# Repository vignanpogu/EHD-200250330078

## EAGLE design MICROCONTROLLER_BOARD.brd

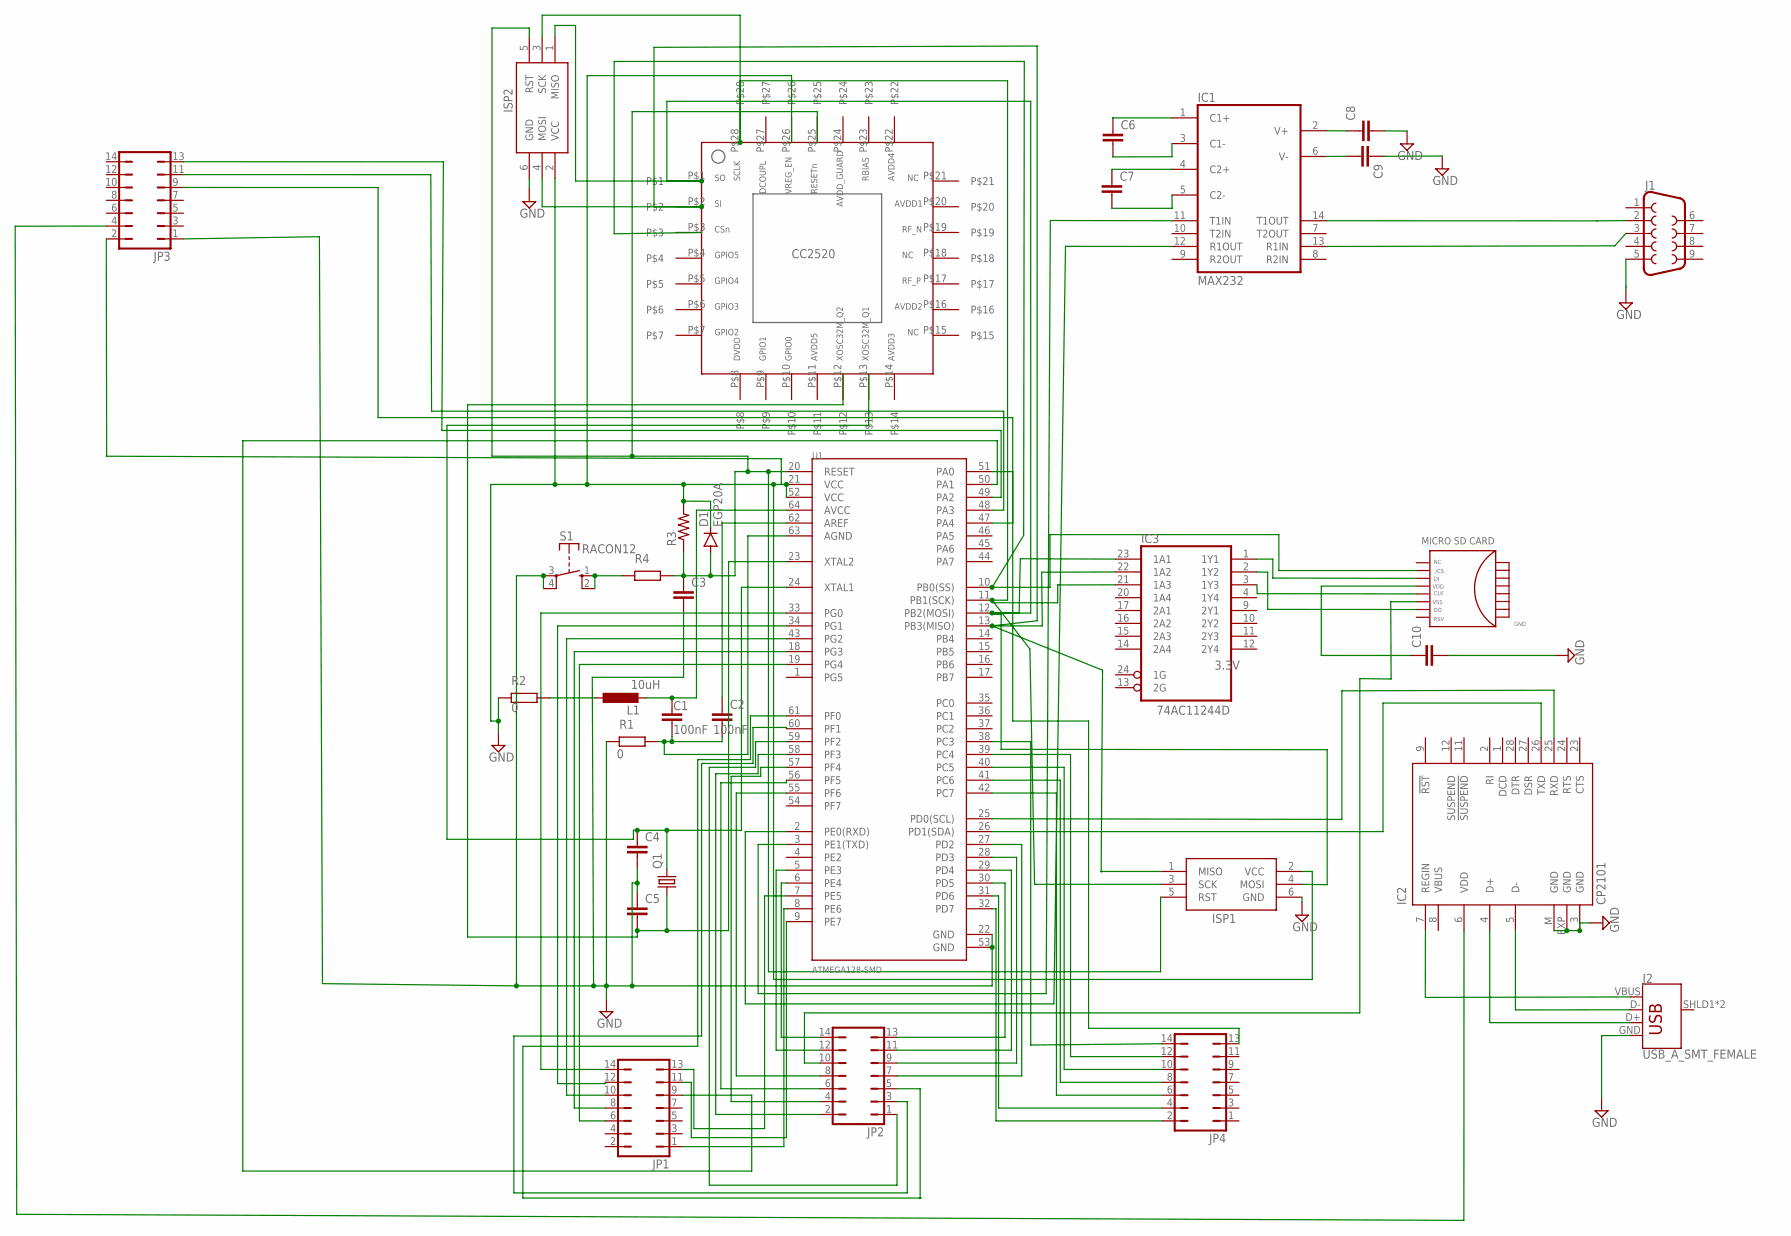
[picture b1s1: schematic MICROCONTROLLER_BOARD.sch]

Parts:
C1, C2, C4, C5: C2,5-3; C2.5-3
C3, C6, C7, C8, C9, C10: C7.5/3; C7.5B3
D1: EGP20A; DO15-12
IC1: MAX232; DIL16
IC2: CP2101; MLP28
IC3: 74AC11244D; SO24W
ISP1, ISP2: AVRISP-6; AVRISP
J1: DB9FEMALE; DB9
J2: USB_A_SMT_FEMALE; USB-A-S-SILK-FEMALE
JP1, JP2, JP3, JP4: JP7Q
L1: L-EU0204/5; 0204/5
Q1: CRYSTALHC49U-V; HC49U-V
R3: R-US_VTA55; VTA55
S1: RACON12
U1: ATMEGA128-SMD; TQFP64_14X14MM
U$1: SD-CARD
U$2: CC2520

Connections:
3.3V: C10.1, U$1.P$4
5V: C3.2, C4.2, C5.1, D1.C, IC1.15 (GND), IC3.5 (GND), IC3.6 (GND), IC3.7 (GND), IC3.8 (GND), ISP1.2 (VCC), ISP2.2 (VCC), JP3.1, JP3.2, R3.2, S1.3, S1.4, U1.21 (VCC), U1.22 (GND), U1.52 (VCC), U1.53 (GND), U$2.P$26
GND: C8.2, C9.1, C10.2, IC2.3 (GND), IC2.EXP (GND), IC2.M (GND), ISP1.6 (GND), ISP2.6 (GND), J1.5, J2.GND
unnamed: C2.1, U1.62 (AREF)
unnamed: C1.2, C2.2, U1.63 (AGND)
unnamed: C1.1, L1.2, U1.64 (AVCC)
unnamed: S1.1 (S), S1.2 (S)
unnamed: C6.1, IC1.1 (C1+)
unnamed: U1.10 (PB0(SS)), U$1.P$2, U$2.P$3
unnamed: C4.1, Q1.2, U1.24 (XTAL1), U$2.P$13
unnamed: C5.2, Q1.1, U1.23 (XTAL2), U$2.P$12
unnamed: IC3.22 (1A2), ISP1.1 (MISO), ISP2.4 (MOSI), U1.13 (PB3(MISO)), U$2.P$2
unnamed: IC3.23 (1A1), ISP1.4 (MOSI), ISP2.1 (MISO), U1.12 (PB2(MOSI)), U$2.P$1
unnamed: IC3.21 (1A3), ISP1.3 (SCK), ISP2.3 (SCK), U1.11 (PB1(SCK)), U$2.P$28
unnamed: C9.2, IC1.6 (V-)
unnamed: C8.1, IC1.2 (V+)
unnamed: C7.1, IC1.4 (C2+)
unnamed: C6.2, IC1.3 (C1-)
unnamed: C7.2, IC1.5 (C2-)
unnamed: IC2.25 (RXD), U1.25 (PD0(SCL))
unnamed: IC1.11 (T1IN), U1.3 (PE1(TXD))
unnamed: IC1.12 (R1OUT), U1.2 (PE0(RXD))
unnamed: IC3.3 (1Y3), U$1.P$5
unnamed: JP2.5, U1.61 (PF0)
unnamed: IC2.5 (D-), J2.D-
unnamed: JP2.3, U1.60 (PF1)
unnamed: IC2.4 (D+), J2.D+
unnamed: IC2.7 (REGIN), J2.VBUS
unnamed: IC1.14 (T1OUT), J1.2
unnamed: IC1.13 (R1IN), J1.3
unnamed: C3.1, D1.A, ISP1.5 (RST), ISP2.5 (RST), R3.1, U1.20 (RESET), U$2.P$25
unnamed: IC2.26 (TXD), U1.26 (PD1(SDA))
unnamed: IC3.1 (1Y1), U$1.P$3
unnamed: IC3.2 (1Y2), U$1.P$7
unnamed: JP2.12, U1.5 (PE3)
unnamed: JP2.14, U1.6 (PE4)
unnamed: JP4.2, U1.32 (PD7)
unnamed: JP4.4, U1.31 (PD6)
unnamed: JP4.12, U1.39 (PC4)
unnamed: JP4.10, U1.40 (PC5)
unnamed: JP4.8, U1.41 (PC6)
unnamed: JP4.6, U1.42 (PC7)
unnamed: JP4.13, U1.51 (PA0)
unnamed: JP1.11, U1.9 (PE7)
unnamed: JP1.1, U1.8 (PE6)
unnamed: JP1.13, U1.7 (PE5)
unnamed: JP1.9, U1.50 (PA1)
unnamed: JP4.14, U1.38 (PC3)
unnamed: JP1.14, U1.33 (PG0)
unnamed: JP1.12, U1.34 (PG1)
unnamed: JP1.10, U1.43 (PG2)
unnamed: JP1.8, U1.18 (PG3)
unnamed: JP1.6, U1.19 (PG4)
unnamed: JP2.13, U1.30 (PD5)
unnamed: JP2.11, U1.29 (PD4)
unnamed: JP2.9, U1.28 (PD3)
unnamed: JP2.7, U1.27 (PD2)
unnamed: JP2.1, U1.59 (PF2)
unnamed: JP2.2, U1.58 (PF3)
unnamed: JP2.4, U1.57 (PF4)
unnamed: JP2.6, U1.56 (PF5)
unnamed: JP2.8, U1.55 (PF6)
unnamed: JP2.10, U$1.P$6
unnamed: JP3.13, U1.49 (PA2)
unnamed: JP3.11, U1.48 (PA3)
unnamed: JP3.9, U1.47 (PA4)
unnamed: IC2.6 (VDD), JP3.4
VCC: IC1.16 (VCC), IC3.18 (VCC), IC3.19 (VCC)

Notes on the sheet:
100nF
10uH

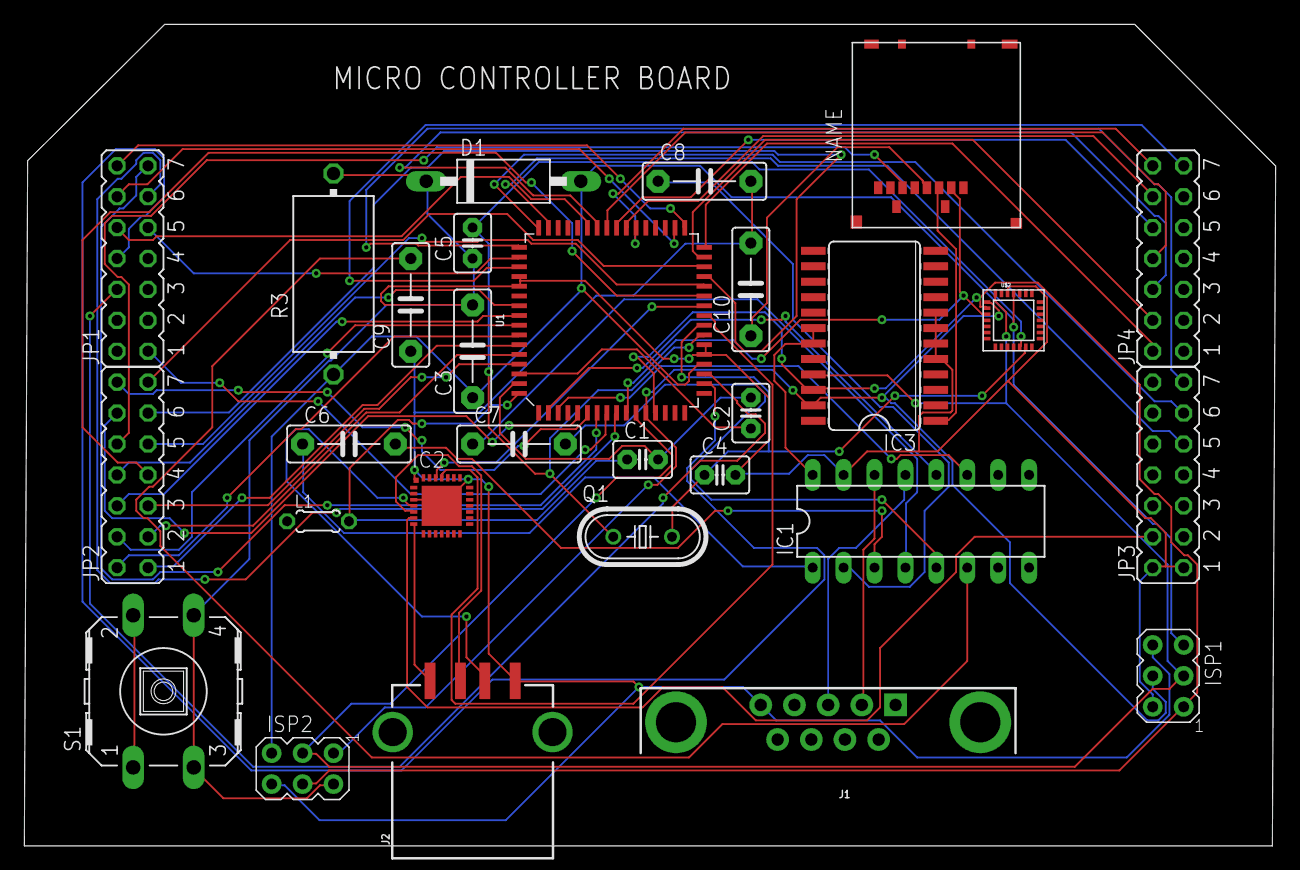
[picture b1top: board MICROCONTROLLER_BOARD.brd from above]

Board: 2 copper layers, 102.8 x 67.5 mm, 29 parts (0 on the bottom side), 68 nets.

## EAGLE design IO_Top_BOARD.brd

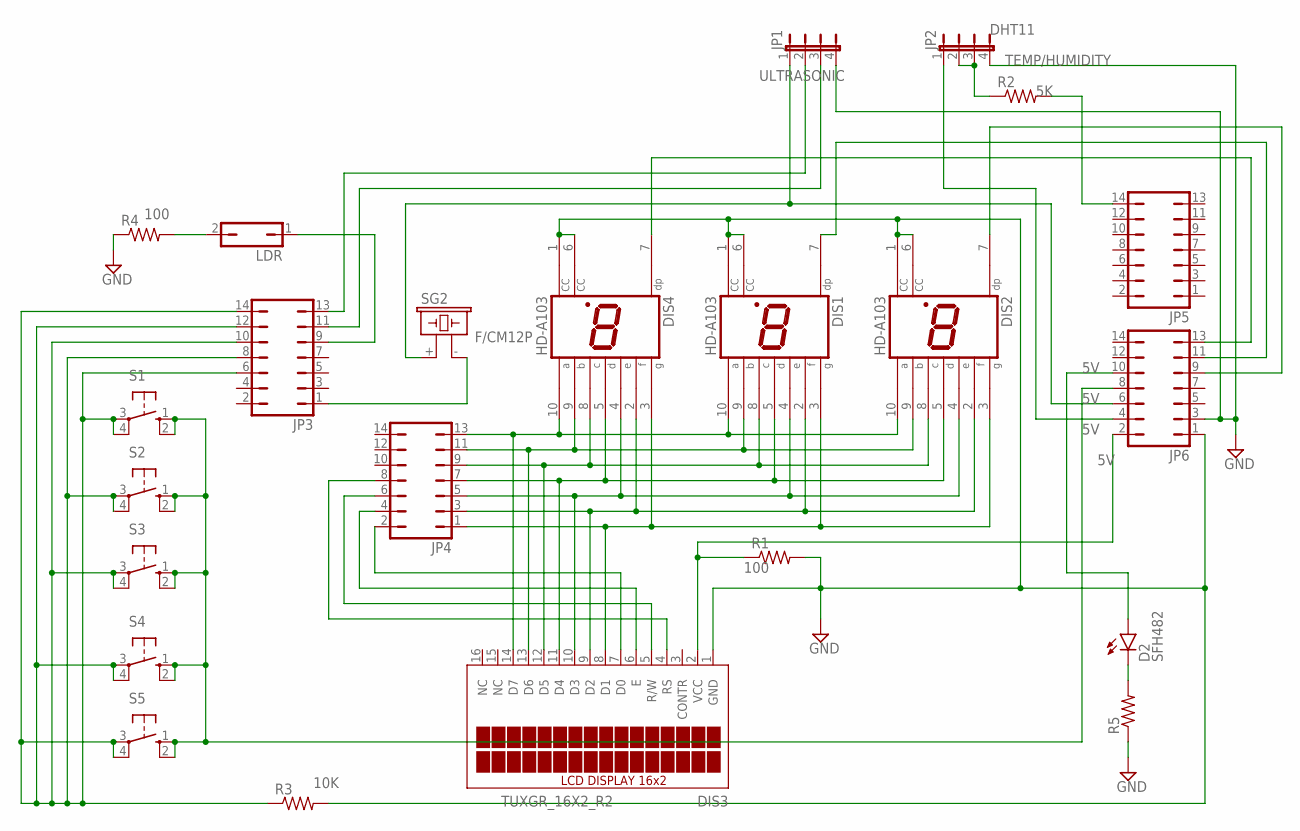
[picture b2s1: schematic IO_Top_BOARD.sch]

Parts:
D2: SFH482
DIS1, DIS2, DIS4: HD-A103; HDSP-A
DIS3: TUXGR_16X2_R2
JP1, JP2: JP4E; JP4
JP3, JP4, JP5, JP6: JP7Q
LDR: JP1Q; JP1
R1, R2, R3, R4, R5: R-US_0204/2V; 0204V
S1, S2, S3, S4, S5: 10-XX; B3F-10XX
SG2: F/CM12P

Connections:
5V: JP1.1, JP6.6, SG2.+ (1)
GND: DIS1.1 (CC), DIS1.6 (CC), DIS2.1 (CC), DIS2.6 (CC), DIS3.1 (GND), DIS4.1 (CC), DIS4.6 (CC), JP1.4, JP2.4, JP6.1, JP6.3, R1.2, R3.2, R4.1, R5.1; also elsewhere on the board
unnamed: JP3.1, SG2.- (2)
unnamed: JP2.2, JP2.3, R2.1
unnamed 6: DIS1.3 (G), DIS2.3 (G), DIS3.8 (D1), DIS4.3 (G), JP4.1; also elsewhere on the board
unnamed 7: DIS1.2 (F), DIS2.2 (F), DIS3.9 (D2), DIS4.2 (F), JP4.3; also elsewhere on the board
unnamed 8: DIS1.4 (E), DIS2.4 (E), DIS3.10 (D3), DIS4.4 (E), JP4.5; also elsewhere on the board
unnamed 9: DIS1.5 (D), DIS2.5 (D), DIS3.11 (D4), DIS4.5 (D), JP4.7; also elsewhere on the board
unnamed 10: DIS1.8 (C), DIS2.8 (C), DIS3.12 (D5), DIS4.8 (C), JP4.9; also elsewhere on the board
unnamed 11: DIS1.9 (B), DIS2.9 (B), DIS3.13 (D6), DIS4.9 (B), JP4.11; also elsewhere on the board
unnamed 12: DIS1.10 (A), DIS2.10 (A), DIS3.14 (D7), DIS4.10 (A), JP4.13; also elsewhere on the board
unnamed 13: DIS3.7 (D0), JP4.2; also elsewhere on the board
unnamed 14: DIS3.2 (VCC), JP6.2, R1.1; also elsewhere on the board
unnamed: JP1.3, JP3.11
unnamed 16: DIS3.6 (E), JP4.4; also elsewhere on the board
unnamed 17: DIS3.5 (R/W), JP4.6; also elsewhere on the board
unnamed 18: DIS3.4 (RS), JP4.8; also elsewhere on the board
unnamed: JP3.6, JP3.8, JP3.10, JP3.12, JP3.14, R3.1, S1.3, S1.4 (P1), S2.3, S2.4 (P1), S3.3, S3.4 (P1), S4.3, S4.4 (P1), S5.3, S5.4 (P1)
unnamed: JP1.2, JP3.13
unnamed: JP5.14, R2.2
unnamed: JP3.9, LDR.1
unnamed: LDR.2, R4.2
unnamed: JP2.1, JP6.4
unnamed: JP6.8, S1.1 (S), S1.2 (S1), S2.1 (S), S2.2 (S1), S3.1 (S), S3.2 (S1), S4.1 (S), S4.2 (S1), S5.1 (S), S5.2 (S1)
unnamed: D2.K (C), R5.2
unnamed: D2.A, JP6.10
unnamed: DIS4.7 (DP), JP6.13
unnamed: DIS1.7 (DP), JP6.11
unnamed: DIS2.7 (DP), JP6.9

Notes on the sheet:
100
ULTRASONIC
TEMP/HUMIDITY
DHT11
10K

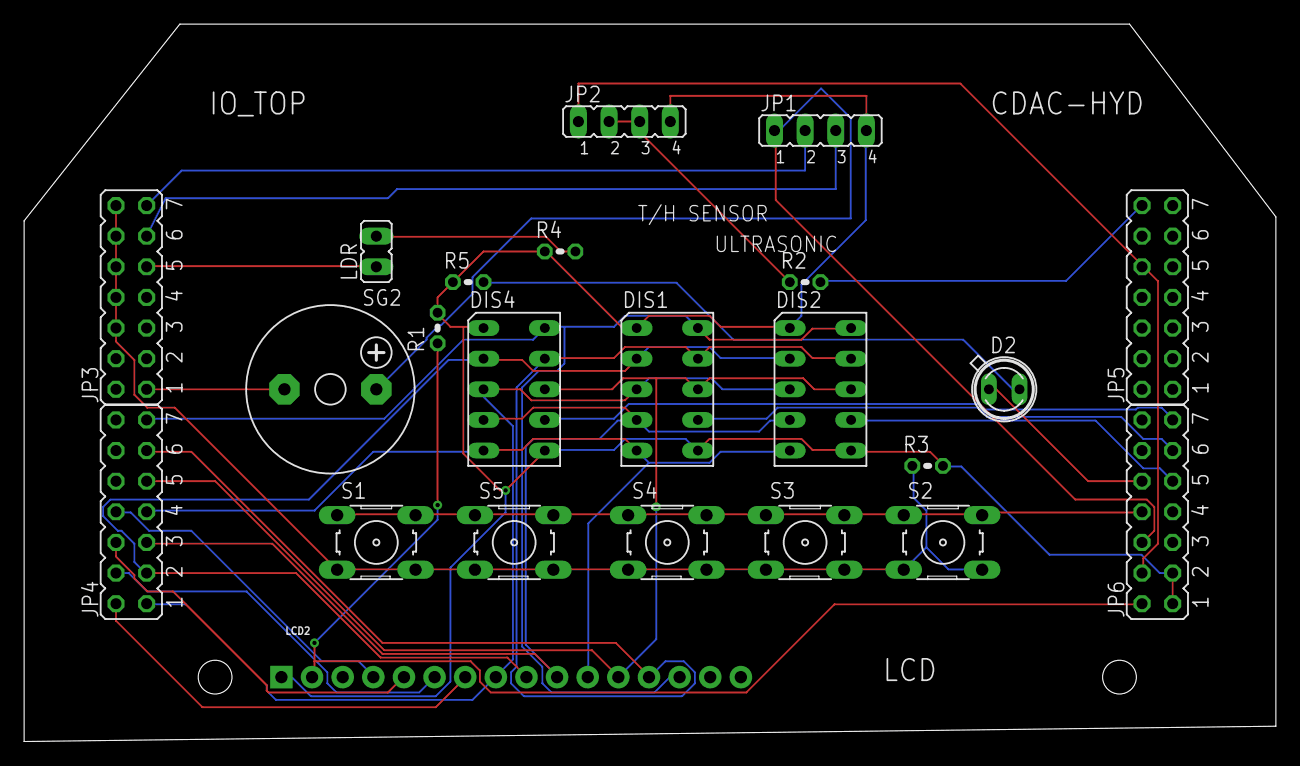
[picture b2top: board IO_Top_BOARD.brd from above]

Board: 2 copper layers, 103.8 x 59.5 mm, 23 parts (0 on the bottom side), 29 nets.

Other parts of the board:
LCD2: LCD-16X2NOSILK; LCD-16X2_NOSILK

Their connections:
GND: LCD2.1; also elsewhere on the board
unnamed 6: LCD2.8; also elsewhere on the board
unnamed 7: LCD2.9; also elsewhere on the board
unnamed 8: LCD2.10; also elsewhere on the board
unnamed 9: LCD2.11; also elsewhere on the board
unnamed 10: LCD2.12; also elsewhere on the board
unnamed 11: LCD2.13; also elsewhere on the board
unnamed 12: LCD2.14; also elsewhere on the board
unnamed 13: LCD2.7; also elsewhere on the board
unnamed 14: LCD2.2; also elsewhere on the board
unnamed 16: LCD2.6; also elsewhere on the board
unnamed 17: LCD2.5; also elsewhere on the board
unnamed 18: LCD2.4; also elsewhere on the board

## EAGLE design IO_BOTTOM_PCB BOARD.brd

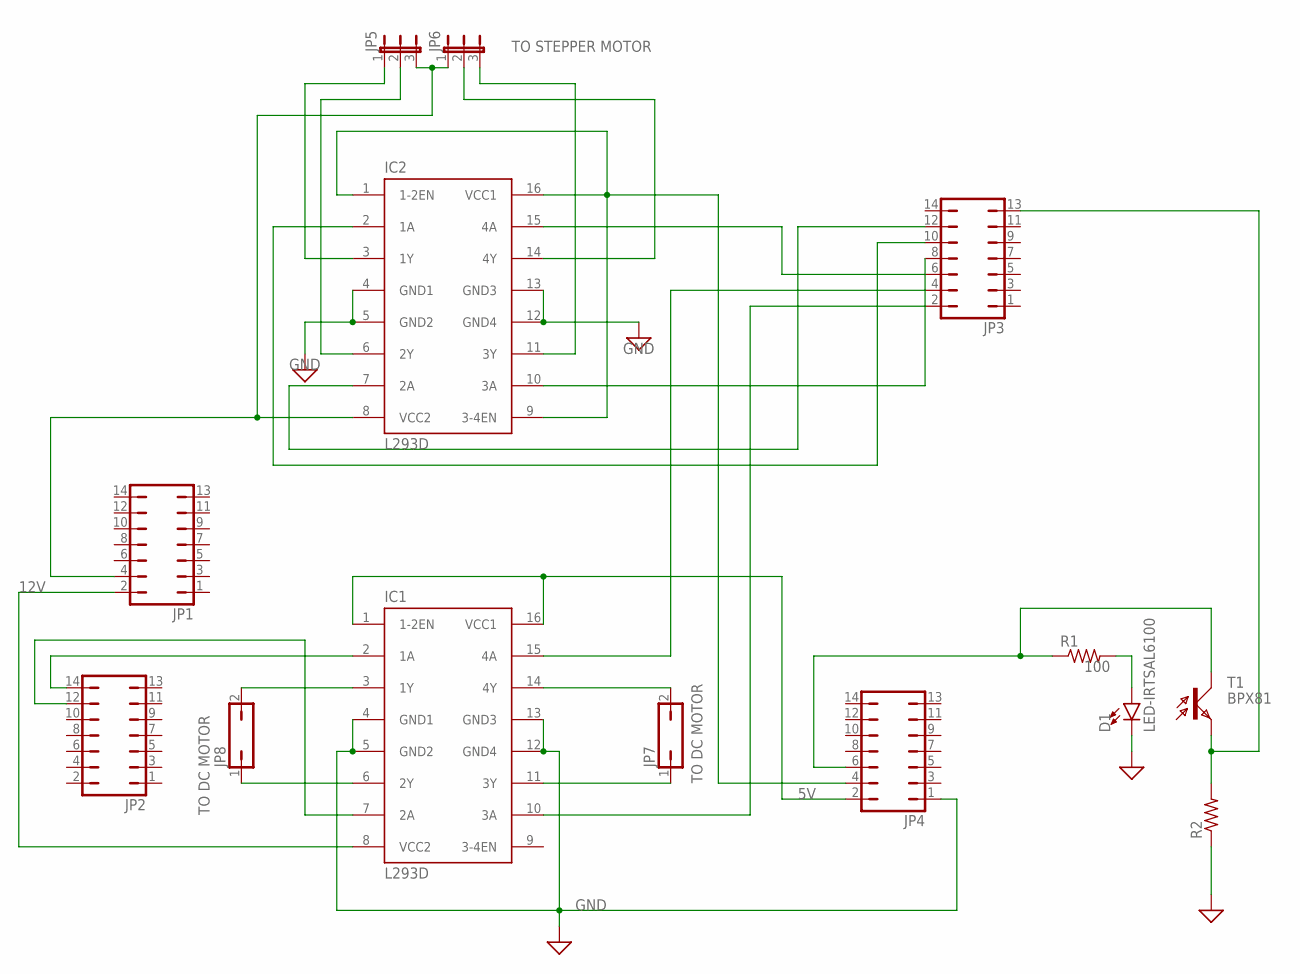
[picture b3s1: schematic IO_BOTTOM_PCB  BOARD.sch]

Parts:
D1: LED-IRTSAL6100; LED_5MM
IC1, IC2: L293D; DIL16
JP1, JP2, JP3, JP4: JP7Q
JP5, JP6: JP2E; JP2
JP7, JP8: JP1Q; JP1
R1, R2: R-US_0204/2V; 0204V
T1: BPX81

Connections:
5V: IC1.8 (VCC2), JP1.2
GND: D1.K (C), IC1.4 (GND1), IC1.5 (GND2), IC1.12 (GND4), IC1.13 (GND3), IC2.4 (GND1), IC2.5 (GND2), IC2.12 (GND4), IC2.13 (GND3), JP4.1, R2.1
unnamed: IC1.3 (1Y), JP8.2
unnamed: IC1.6 (2Y), JP8.1
unnamed: IC1.11 (3Y), JP7.1
unnamed: IC1.14 (4Y), JP7.2
unnamed: IC1.2 (1A), JP2.14
unnamed: IC1.7 (2A), JP2.12
unnamed: IC1.1 (1-2EN), IC1.16 (VCC1), JP4.2
unnamed: IC1.15 (4A), JP3.4
unnamed: IC1.10 (3A), JP3.2
unnamed: IC2.15 (4A), JP3.6
unnamed: IC2.10 (3A), JP3.8
unnamed: IC2.2 (1A), JP3.10
unnamed: IC2.7 (2A), JP3.12
unnamed: IC2.1 (1-2EN), IC2.9 (3-4EN), IC2.16 (VCC1), JP4.4
unnamed: IC2.6 (2Y), JP5.2
unnamed: IC2.3 (1Y), JP5.1
unnamed: IC2.11 (3Y), JP6.3
unnamed: IC2.8 (VCC2), JP1.4, JP5.3, JP6.1
unnamed: IC2.14 (4Y), JP6.2
unnamed: D1.A, R1.2
unnamed: JP3.13, R2.2, T1.E
unnamed: JP4.6, R1.1, T1.C

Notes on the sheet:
12V
GND
TO STEPPER MOTOR
TO DC MOTOR
100

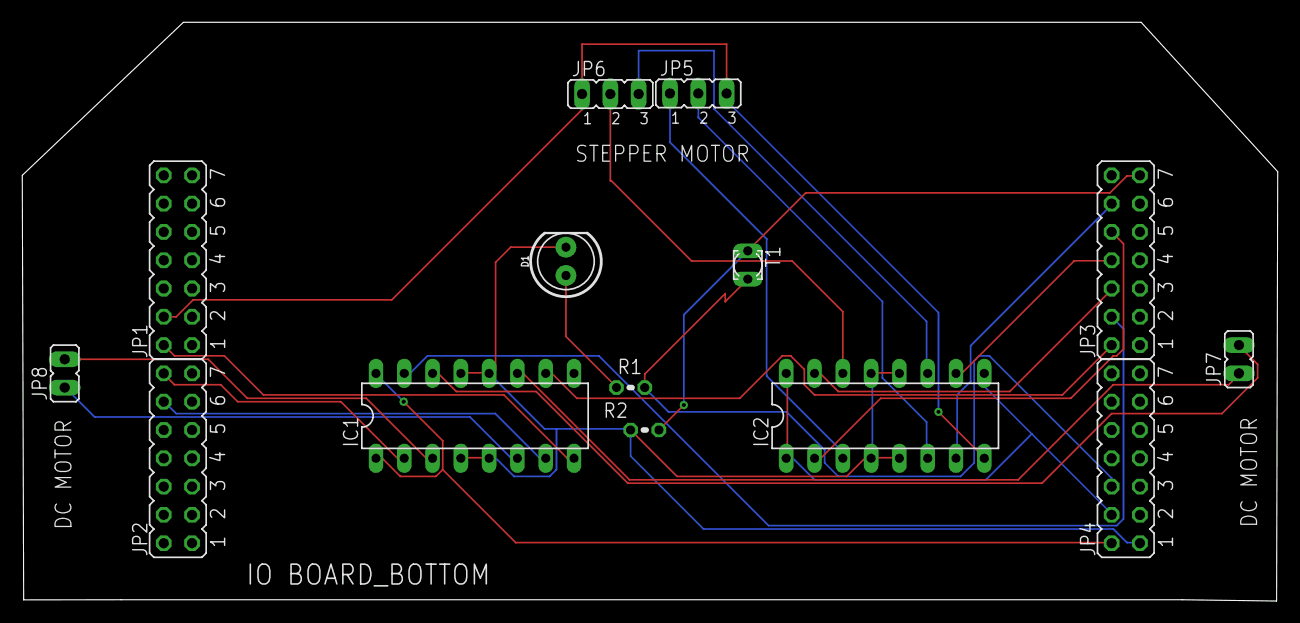
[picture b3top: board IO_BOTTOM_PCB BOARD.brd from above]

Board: 2 copper layers, 112.7 x 52.0 mm, 14 parts (0 on the bottom side), 24 nets.

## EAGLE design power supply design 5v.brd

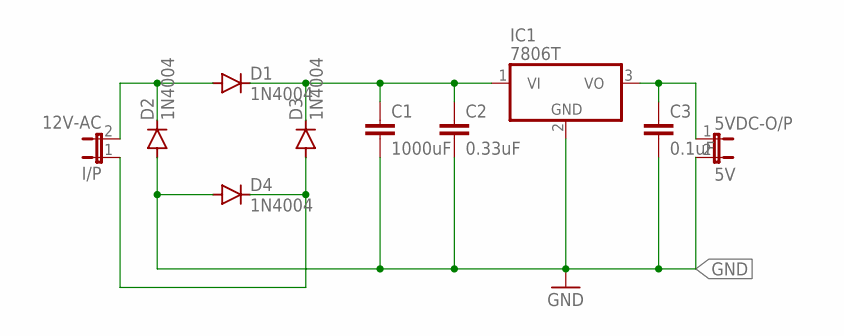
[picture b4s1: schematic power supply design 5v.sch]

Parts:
5VDC-O/P: 5V; JP1
C1: 1000uF; C2.5-3
C2: 0.33uF; C2.5-3
C3: 0.1uF; C2.5-3
D1, D2, D3, D4: 1N4004; DO41-10
I/P: 12V-AC; JP1
IC1: 7806T; TO220H

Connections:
GND: 5VDC-O/P.2, C1.2, C2.2, C3.2, D2.A, D4.A, IC1.2 (GND)
unnamed: D1.A, D2.C, I/P.2
unnamed: C1.1, C2.1, D1.C, D3.C, IC1.1 (VI)
unnamed: D3.A, D4.C, I/P.1
unnamed: 5VDC-O/P.1, C3.1, IC1.3 (VO)

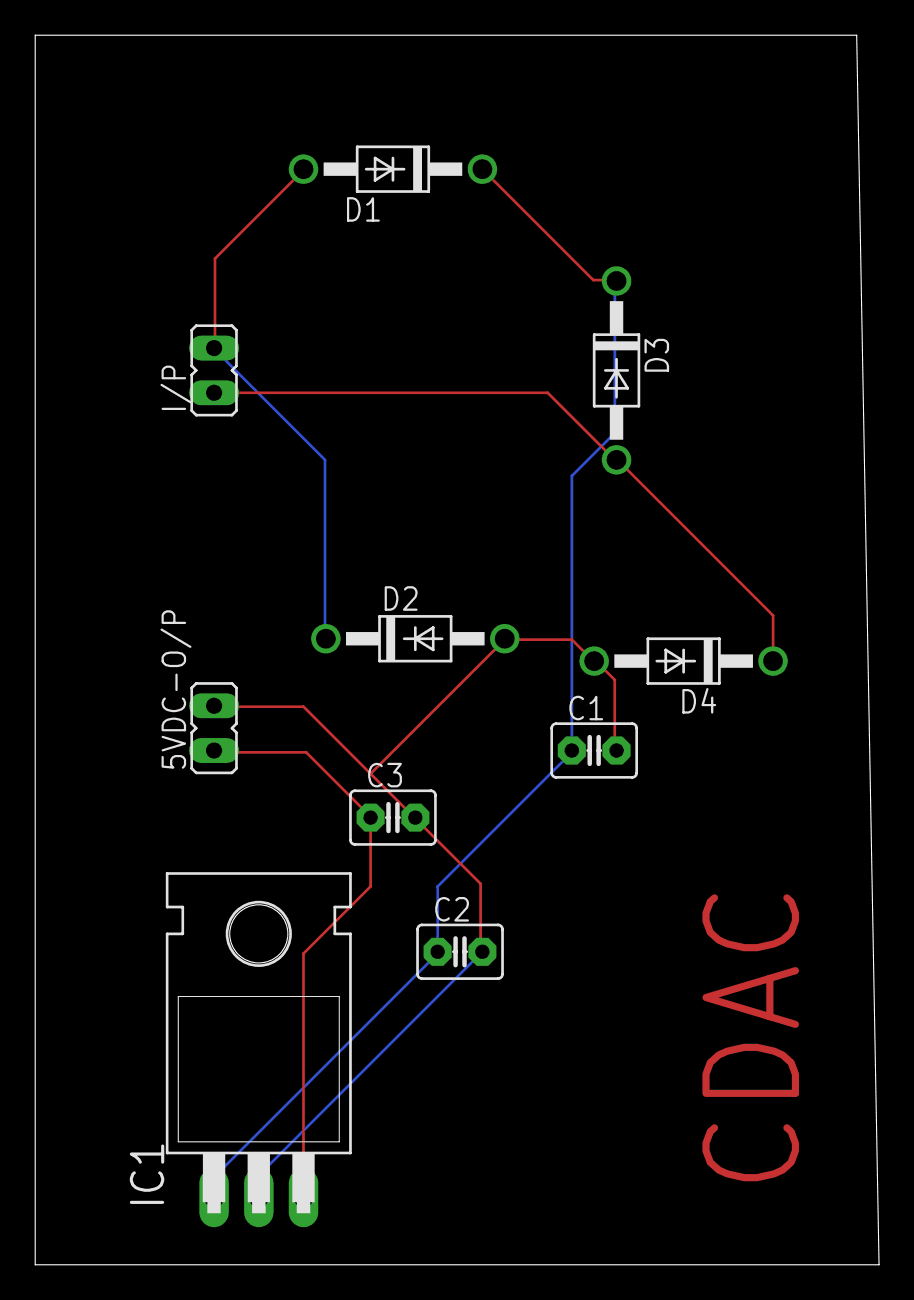
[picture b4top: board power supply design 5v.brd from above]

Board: 2 copper layers, 47.9 x 69.8 mm, 10 parts (0 on the bottom side), 5 nets.

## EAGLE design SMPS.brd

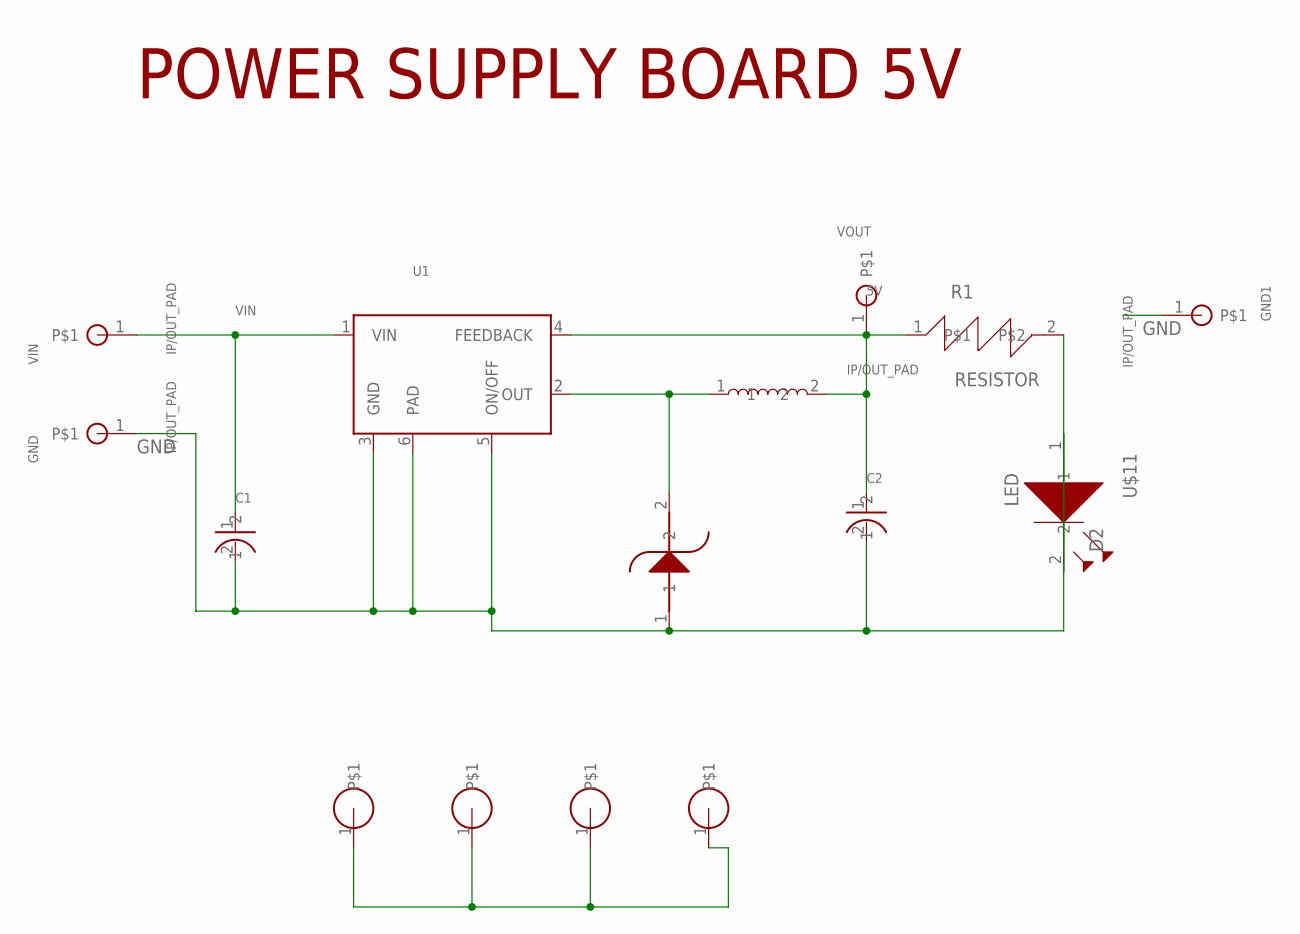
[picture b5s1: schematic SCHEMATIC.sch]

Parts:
C1: 100uF; CAPACITOR
C2: 1000uF; CAPACITOR
D1: 1N5822; 1N5822_SMD
GND, GND1: IP/OUT_PAD
L1: 100uH; INDUCTOR
MH1, MH2, MH3, MH4: MH_HOLE
R1: RESISTOR; 0805_RESISTOR
U1: LM2576
U$11: LED; 8085LED
VIN: IP/OUT_PAD
VOUT: IP/OUT_PAD

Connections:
5V: C2.1, L1.2, R1.1, U1.4 (FEEDBACK), VOUT.1
D2: R1.2, U$11.2
GND: C1.2, C2.2, D1.1, GND.1, GND1.1, U1.3 (GND), U1.5 (ON/OFF), U1.6 (PAD), U$11.1
unnamed: MH1.1, MH2.1, MH3.1, MH4.1
unnamed: D1.2, L1.1, U1.2 (OUT)
VIN: C1.1, U1.1 (VIN), VIN.1

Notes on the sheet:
POWER SUPPLY BOARD 5V

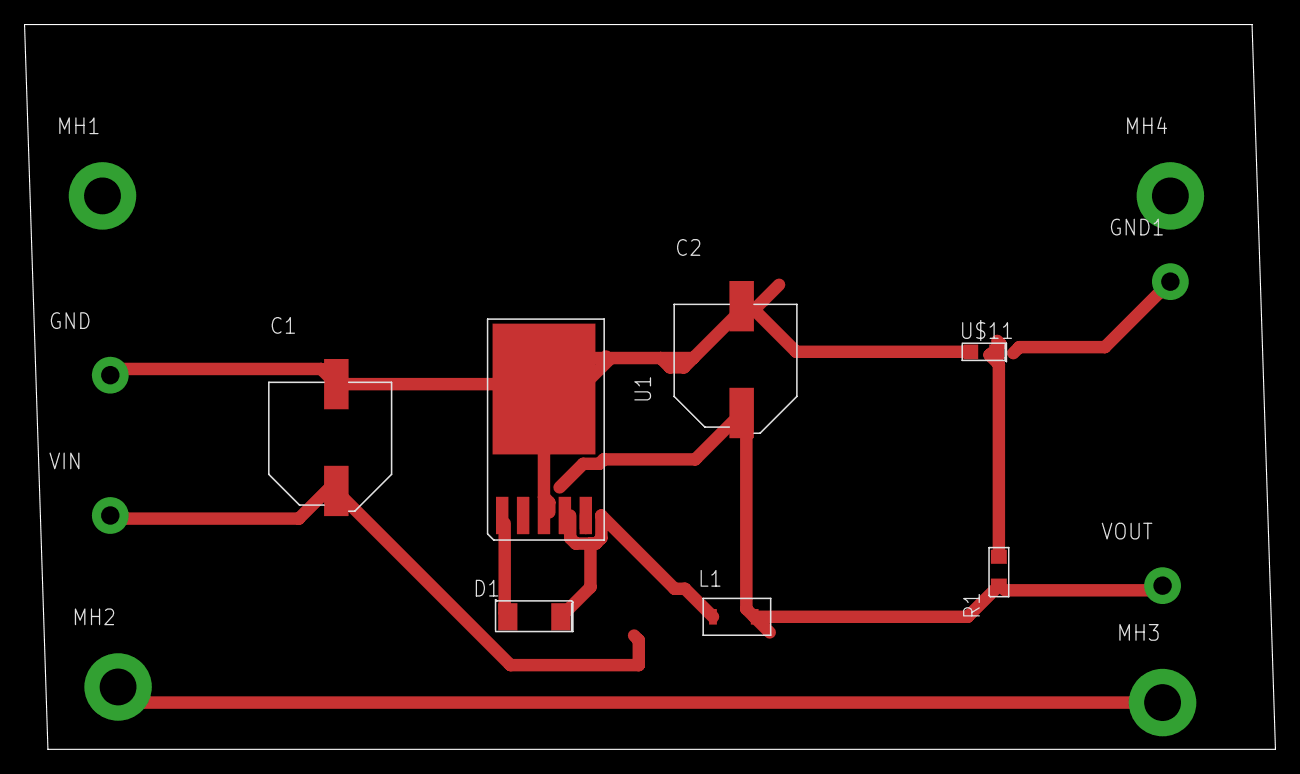
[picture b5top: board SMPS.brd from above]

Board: 2 copper layers, 101.9 x 59.0 mm, 15 parts (0 on the bottom side), 6 nets.

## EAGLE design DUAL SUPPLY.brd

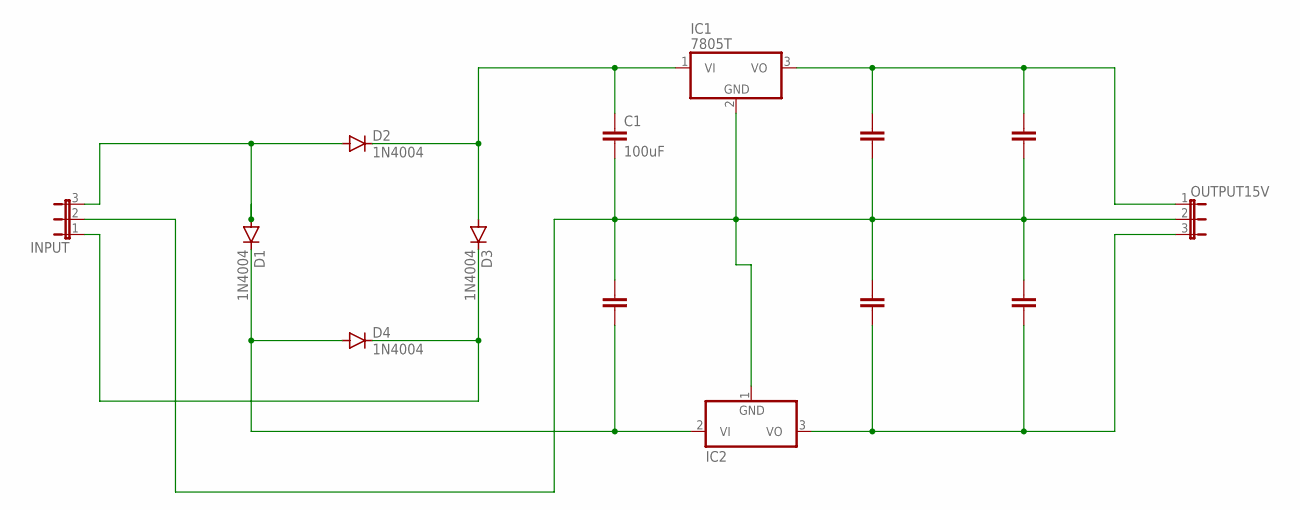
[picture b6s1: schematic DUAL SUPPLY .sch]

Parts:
C1, C2: 100uF; C2.5-3
C3, C4: 10uF; C2.5-3
C5, C6: 0.1uF; C2.5-3
D1, D2, D3, D4: 1N4004; DO41-10
IC1: 7805T; TO220H
IC2: 7905T; TO220H
INPUT: JP2E; JP2
OUTPUT15V: JP2E; JP2

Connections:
C: C1.2, C2.1, C3.2, C4.1, C5.2, C6.1, IC1.2 (GND), IC2.1 (GND), INPUT.2, OUTPUT15V.2
unnamed: D1.A, D2.A, INPUT.3
unnamed: C3.1, C5.1, IC1.3 (VO), OUTPUT15V.1
unnamed: D3.C, D4.C, INPUT.1
unnamed: C2.2, D1.C, D4.A, IC2.2 (VI)
unnamed: C4.2, C6.2, IC2.3 (VO), OUTPUT15V.3
unnamed: C1.1, D2.C, D3.A, IC1.1 (VI)

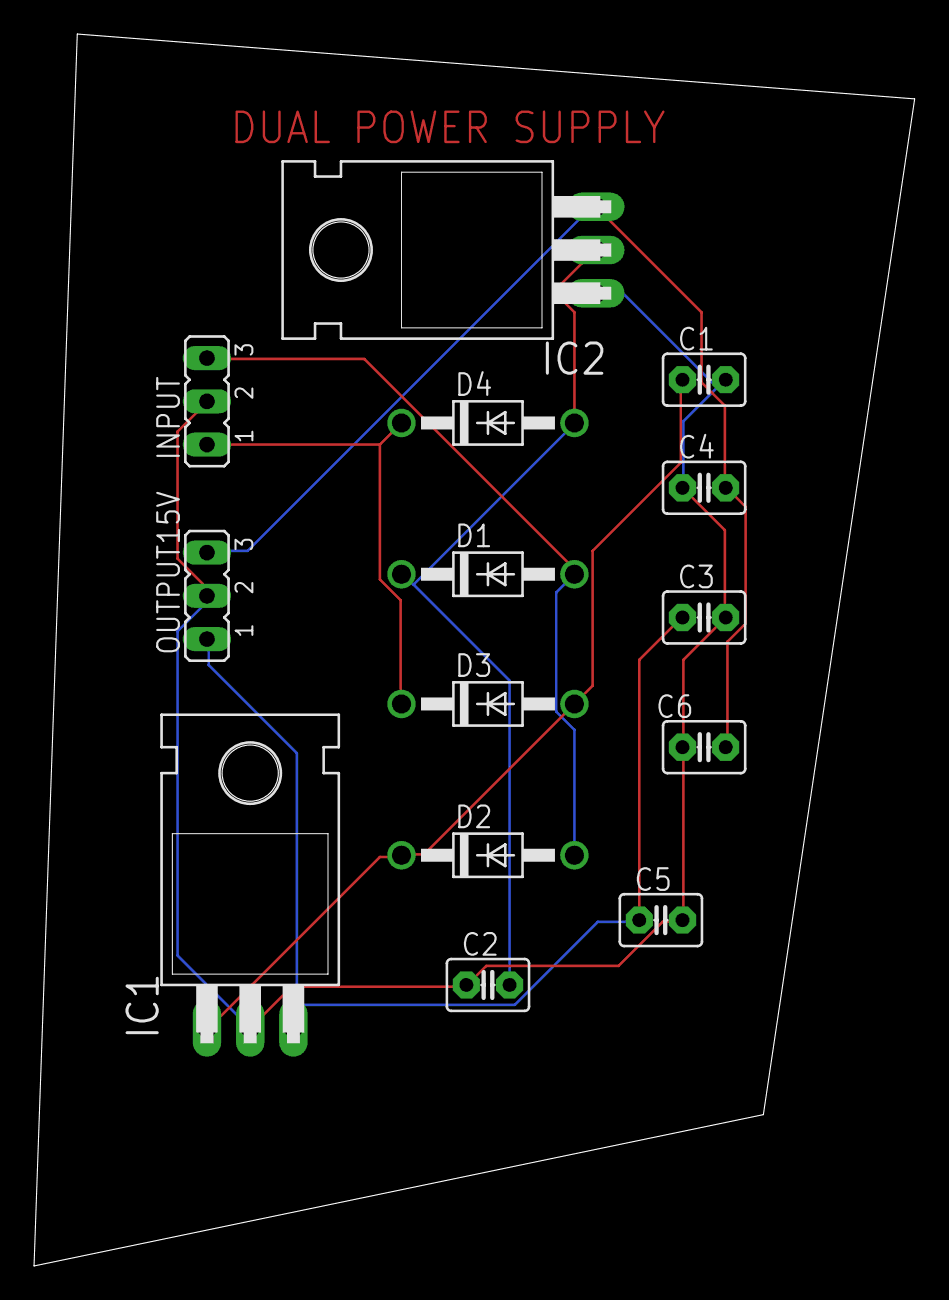
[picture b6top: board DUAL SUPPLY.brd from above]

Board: 2 copper layers, 51.7 x 72.4 mm, 14 parts (0 on the bottom side), 7 nets.

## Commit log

2020-10-09 Rename SMPS(BOT Design).brd to SMPS.brd
2020-10-09 Rename SMPS(BOT Design).sch to SMPS.sch

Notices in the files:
parts and their libraries:
SparkFun-LED: Licensing: Creative Commons ShareAlike 4.0 International - https://creativecommons.org/licenses/by-sa/4.0
